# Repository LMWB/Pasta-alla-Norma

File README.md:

# Pasta_alla_Norma
Circular shaped RGB-LED PCB with integrated Microcontroller and EEPROM

# cubeIDE Setting for evaluate used flash size
```arm-none-eabi-nm --size-sort --print-size "RGB_Ring_LimbusZero.elf" > "RGB_Ring_LimbusZero.sizes"```  

- T / t → Flash (code)  
- R / r → Flash (read-only const)  
- D / d → RAM (with init in Flash)  
- B / b → RAM only (zero-init)  
- W / w → Weak (depends where resolved, often Flash functions)  

# Fassung
E27 bedeutet Edison Fassung 27 mm (siehe Zeichnung).  
Ein zylindrischer Stempel der in die Fassung passt ohne Gewinde, sollte 30mm Lange haben und 24mm Durchmesser.

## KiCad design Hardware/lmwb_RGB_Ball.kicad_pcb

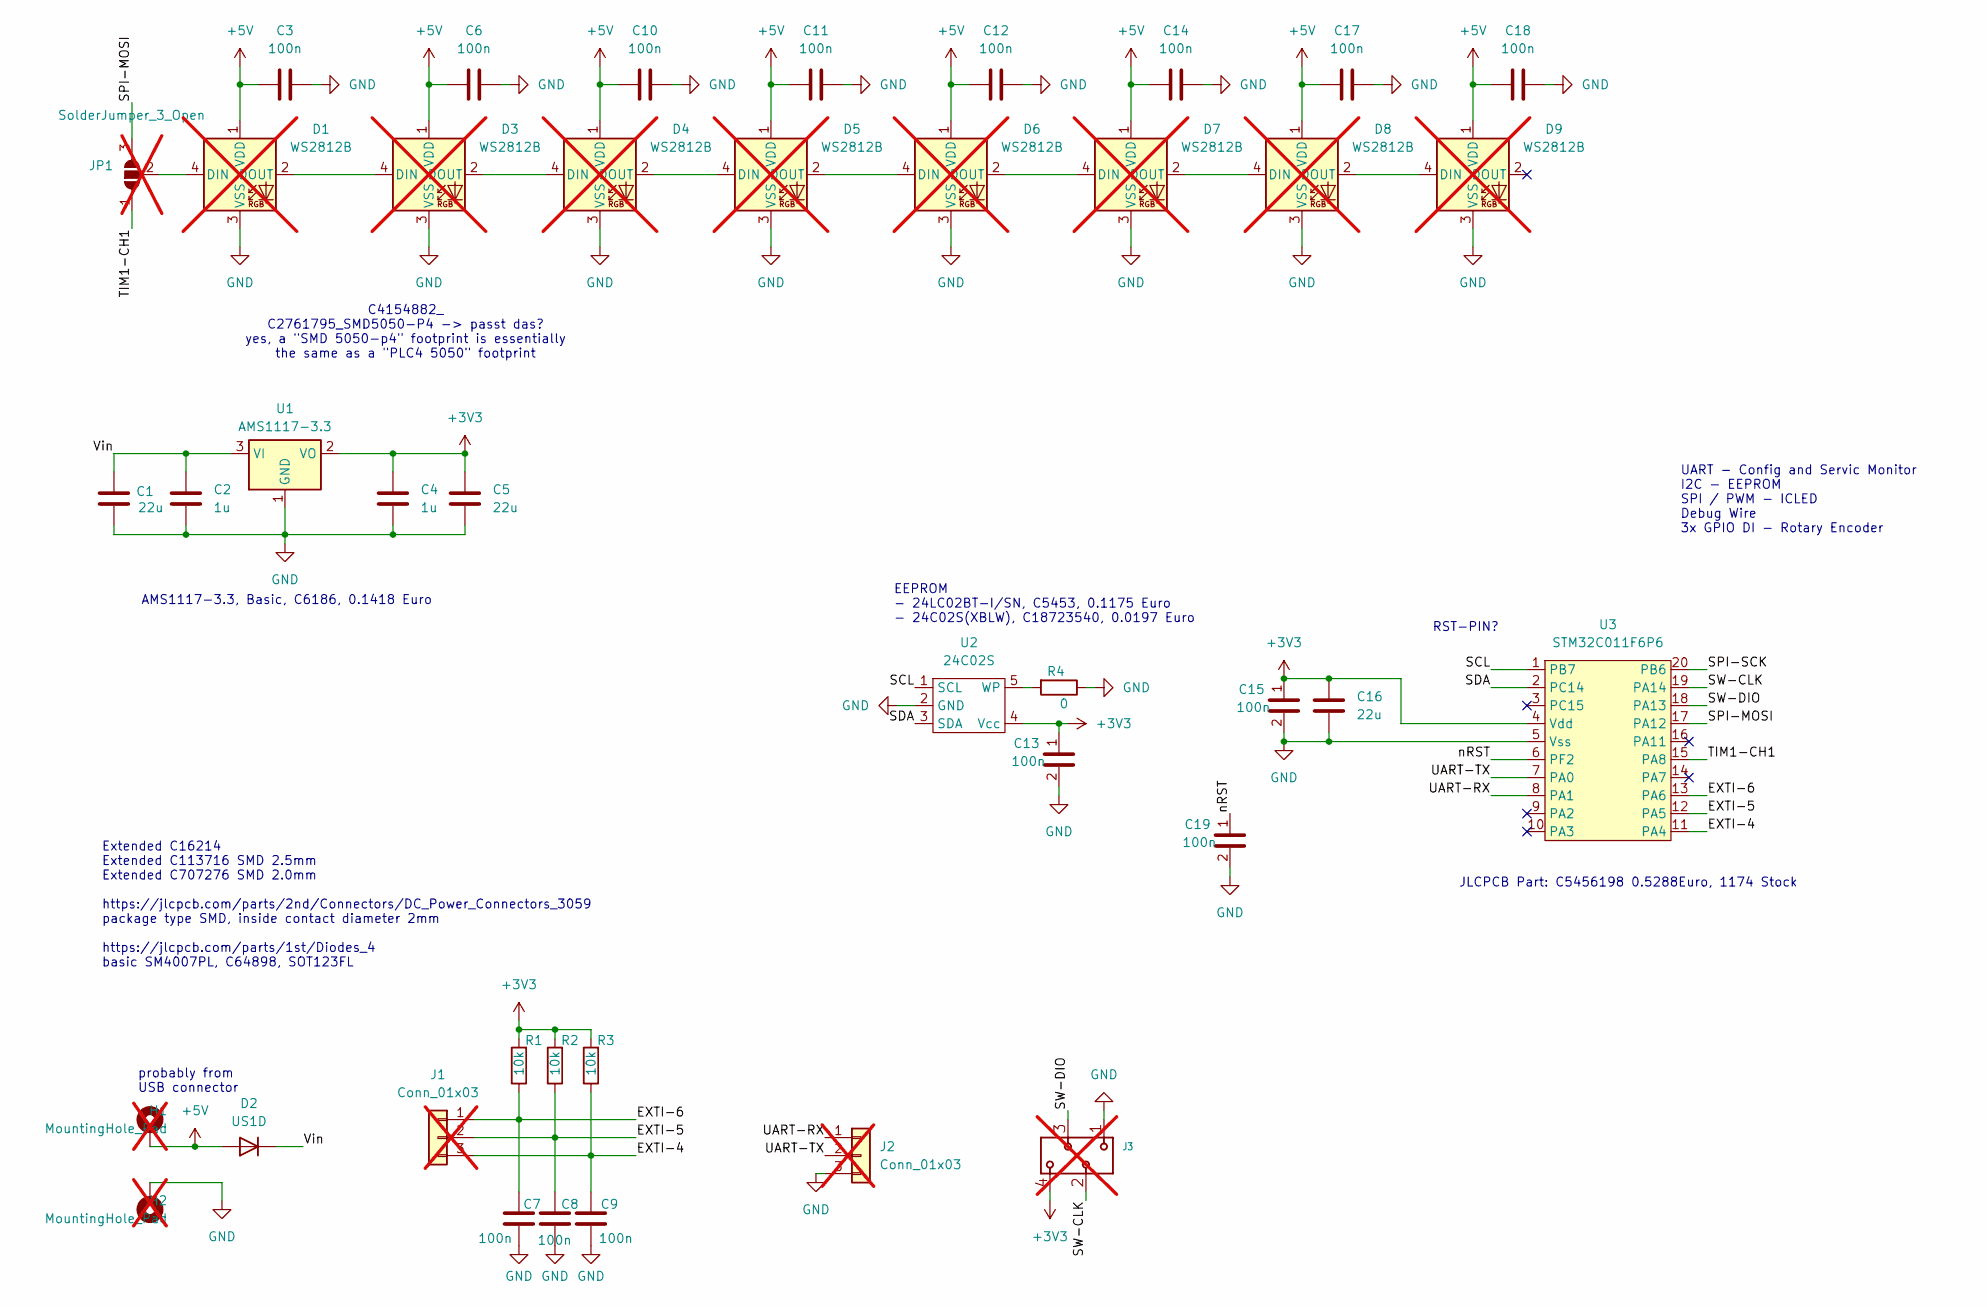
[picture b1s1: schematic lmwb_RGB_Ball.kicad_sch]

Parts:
C1, C5, C16: 22u; C_0805_2012Metric; LCSC PN C45783
C2, C4: 1u; C_0805_2012Metric; LCSC PN C28323
C3, C6, C7, C8, C9, C10, C11, C12, C13, C14, C15, C17, C18, C19: 100n; C_0805_2012Metric; LCSC PN C49678
D1, D3, D4, D5, D6, D7, D8, D9: WS2812B; LED_WS2812B_PLCC4_5.0x5.0mm_P3.2mm; LCSC PN C2761795; not fitted
D2: US1D; D_SMA; LCSC PN C95872
H1, H2: MountingHole_Pad; MountingHole_4.3mm_M4_Pad; not fitted
J1, J2: Conn_01x03; PinHeader_1x03_P2.54mm_Vertical; not fitted
J3: 490107670412_DEBUGGING; not fitted
JP1: SolderJumper_3_Open; SolderJumper-3_P1.3mm_Open_RoundedPad1.0x1.5mm; not fitted
R1, R2, R3: 10k; R_0805_2012Metric; LCSC PN C17414
R4: 0; R_0805_2012Metric; LCSC PN C17477
U1: AMS1117-3.3; SOT-223-3_TabPin2; LCSC PN C6186
U2: 24C02S; SOT-23-5; LCSC PN C18723540
U3: STM32C011F6P6; TSSOP-20_4.4x6.5mm_P0.65mm; LCSC PN C5456198

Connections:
+3V3: C4.1, C5.1, C13.1, C15.1, C16.1, J3.4, R1.2, R2.2, R3.2, U1.2 (VO), U2.4 (Vcc), U3.4 (Vdd)
+5V: C3.1, C6.1, C10.1, C11.1, C12.1, C14.1, C17.1, C18.1, D1.1 (VDD), D2.2 (A), D3.1 (VDD), D4.1 (VDD), D5.1 (VDD), D6.1 (VDD), D7.1 (VDD), D8.1 (VDD), D9.1 (VDD), H1.1
/EXTI-4: C9.1, J1.3, R3.1, U3.11 (PA4)
/EXTI-5: C8.1, J1.2, R2.1, U3.12 (PA5)
/EXTI-6: C7.1, J1.1, R1.1, U3.13 (PA6)
/SCL: U2.1 (SCL), U3.1 (PB7)
/SDA: U2.3 (SDA), U3.2 (PC14)
/SPI-MOSI: JP1.3 (B), U3.17 (PA12)
/SPI-SCK: U3.20 (PB6)
/SW-CLK: J3.2, U3.19 (PA14)
/SW-DIO: J3.3, U3.18 (PA13)
/TIM1-CH1: JP1.1 (A), U3.15 (PA8)
/UART-RX: J2.1, U3.8 (PA1)
/UART-TX: J2.2, U3.7 (PA0)
/Vin: C1.1, C2.1, D2.1 (K), U1.3 (VI)
/nRST: C19.1, U3.6 (PF2)
GND: C1.2, C2.2, C3.2, C4.2, C5.2, C6.2, C7.2, C8.2, C9.2, C10.2, C11.2, C12.2, C13.2, C14.2, C15.2, C16.2, C17.2, C18.2, C19.2, D1.3 (VSS), D3.3 (VSS), D4.3 (VSS), D5.3 (VSS), D6.3 (VSS), D7.3 (VSS), D8.3 (VSS), D9.3 (VSS), H2.1, J2.3, J3.1, R4.1, U1.1 (GND), U2.2 (GND), U3.5 (Vss)
unnamed: D1.4 (DIN), JP1.2 (C)
unnamed: D1.2 (DOUT), D3.4 (DIN)
unnamed: D3.2 (DOUT), D4.4 (DIN)
unnamed: D4.2 (DOUT), D5.4 (DIN)
unnamed: D5.2 (DOUT), D6.4 (DIN)
unnamed: D6.2 (DOUT), D7.4 (DIN)
unnamed: D7.2 (DOUT), D8.4 (DIN)
unnamed: D8.2 (DOUT), D9.4 (DIN)
unnamed: R4.2, U2.5 (WP)

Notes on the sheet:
UART - Config and Servic Monitor I2C - EEPROM SPI / PWM - ICLED Debug Wire 3x GPIO DI - Rotary Encoder
probably from USB connector
EEPROM - 24LC02BT-I/SN, C5453, 0.1175 Euro - 24C02S(XBLW), C18723540, 0.0197 Euro
RST-PIN?
AMS1117-3.3, Basic, C6186, 0.1418 Euro
JLCPCB Part: C5456198 0.5288Euro, 1174 Stock
Extended C16214 Extended C113716 SMD 2.5mm Extended C707276 SMD 2.0mm https://jlcpcb.com/parts/2nd/Connectors/DC_Power_Connectors_3059 package type SMD, inside contact diameter 2mm https://jlcpcb.com/parts/1st/Diodes_4 basic SM4007PL, C64898, SOT123FL
C4154882_ C2761795_SMD5050-P4 -> passt das? yes, a "SMD 5050-p4" footprint is essentially the same as a "PLC4 5050" footprint

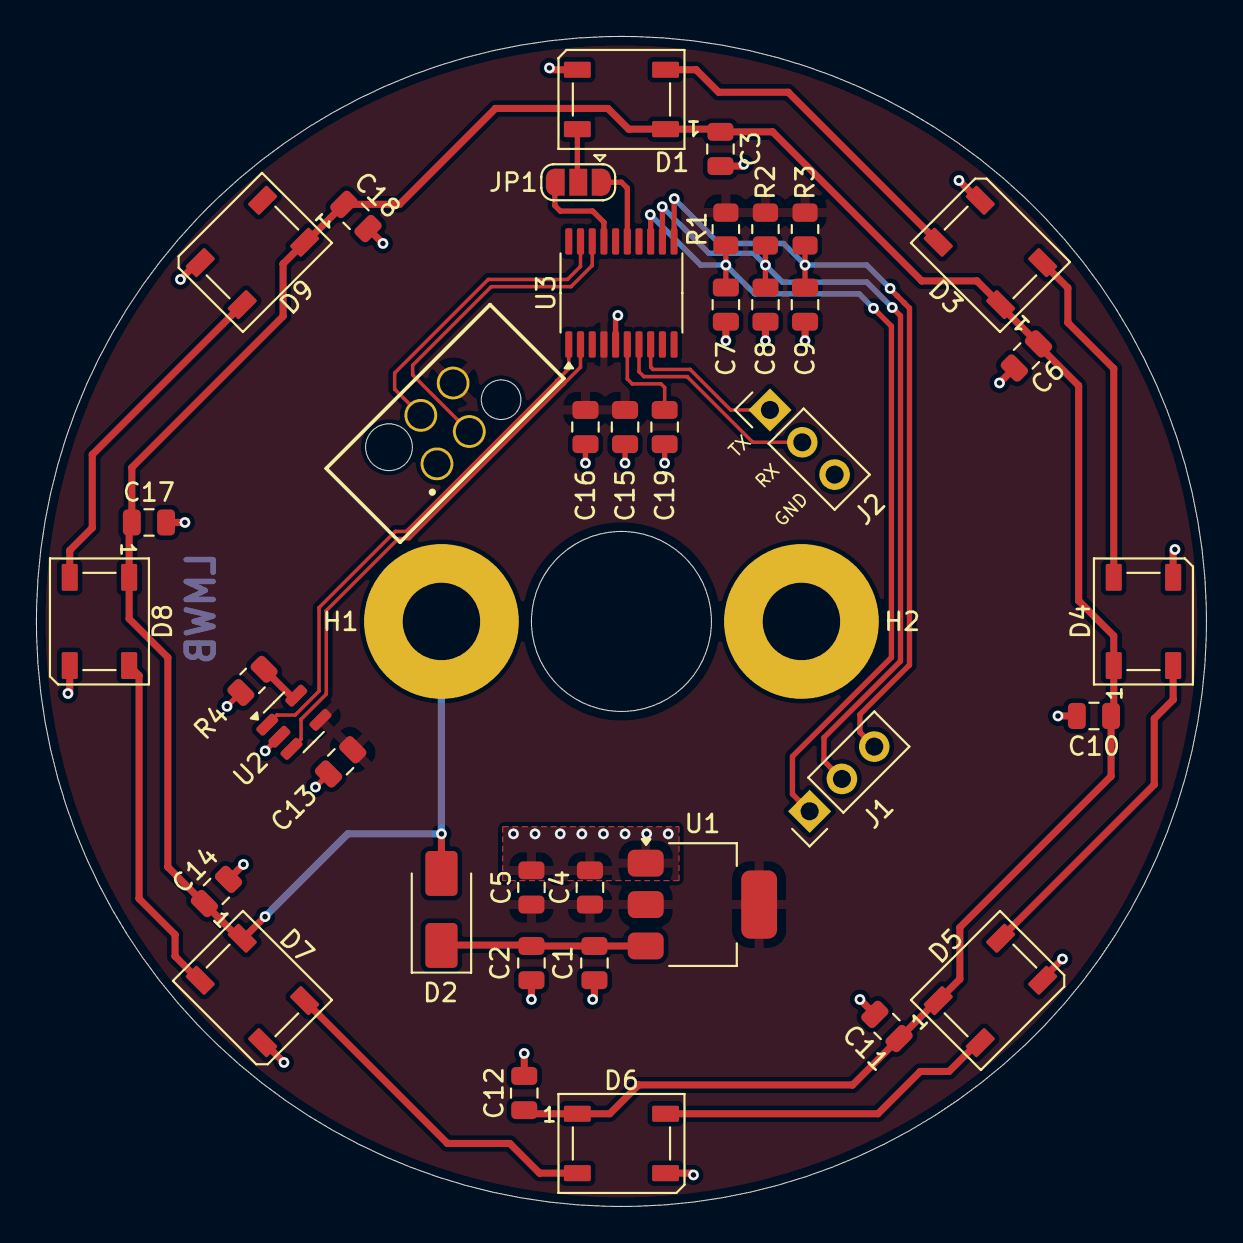
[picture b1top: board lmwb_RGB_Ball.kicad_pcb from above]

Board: 2 copper layers, 65.0 x 65.0 mm, 41 parts (0 on the bottom side), 25 nets.

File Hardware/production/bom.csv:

Designator,Footprint,Quantity,Value,LCSC Part #
"C1, C16, C5",0805,3,22u,C45783
"C10, C11, C12, C13, C14, C15, C17, C18, C19, C3, C6, C7, C8, C9",0805,14,100n,C49678
"C2, C4",0805,2,1u,C28323
D2,D_SMA,1,US1D,C95872
"R1, R2, R3",0805,3,10k,C17414
R4,0805,1,0,C17477
U1,SOT-223-3_TabPin2,1,AMS1117-3.3,C6186
U2,SOT-23-5,1,24C02S,C18723540
U3,TSSOP-20_4.4x6.5mm_P0.65mm,1,STM32C011F6P6,C5456198

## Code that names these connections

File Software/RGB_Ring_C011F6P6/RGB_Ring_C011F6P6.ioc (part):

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Mcu.Name=STM32C011F(4-6)Px
Mcu.Package=TSSOP20
Mcu.UserName=STM32C011F6Px
PA0.Signal=USART1_TX
PA1.Signal=USART1_RX
PA12\ [PA10].Mode=TX_Only_Simplex_Unidirect_Master
PA12\ [PA10].Signal=SPI1_MOSI
PA13.Mode=Serial_Wire
PA13.Signal=DEBUG_SWDIO
PA14-BOOT0.Mode=Serial_Wire
PA14-BOOT0.Signal=DEBUG_SWCLK
PA4.GPIOParameters=GPIO_Label
PA4.GPIO_Label=IN2
PA4.Signal=GPIO_Input
PA5.GPIOParameters=GPIO_Label
PA5.GPIO_Label=OUT1
PA5.Signal=GPIO_Output
PA6.GPIOParameters=GPIO_Label
PA6.GPIO_Label=IN1
PA6.Signal=GPIO_Input
PA8.GPIOParameters=GPIO_Speed,GPIO_PuPd
PA8.GPIO_PuPd=GPIO_PULLUP
PA8.GPIO_Speed=GPIO_SPEED_FREQ_VERY_HIGH
PA8.Signal=S_TIM1_CH1
PB6.GPIOParameters=GPIO_Speed,GPIO_PuPd
PB6.GPIO_PuPd=GPIO_PULLDOWN
PB6.GPIO_Speed=GPIO_SPEED_FREQ_VERY_HIGH
PB6.Mode=TX_Only_Simplex_Unidirect_Master
PB6.Signal=SPI1_SCK
PB7.Signal=I2C1_SCL
PC14-OSCX_IN\ (PC14).Signal=I2C1_SDA
RCC.HSE_VALUE=8000000
RCC.SYSCLKFreq_VALUE=48000000
board=custom

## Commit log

2025-08-28 created project structure
2025-09-14 did some routing
2025-09-14 added freeCAD Model
2025-09-14 did some readme
2025-09-22 added CAD files adn step files
2025-09-22 added LimbusZero cubeMX project
2025-09-22 added C-libraries
2025-09-25 added F04xx project, coded firmware, progress on layout
2025-09-26 progress on layout
2025-09-26 order pcb and assambly
2025-09-28 moved functional code to rgb_ball.c
2025-09-28 removed math.c and created gamma-look-up-table
2025-09-28 modified python script
2025-09-29 modified readme
2025-10-06 added rainbow fade
2025-10-07 added sunstorm loop
2025-10-11 testing sunstorm fade
2025-10-11 LED toggle wrapper
2025-10-11 read / write pin wrapper
2025-10-11 add libs to tarket project
2025-10-11 add application to target project
2025-10-17 software adjustments to fit target PCB
2025-10-17 synch SW changes from target PCB to LimbusZero Dev Platform
2025-10-17 update cubeMX project for SPI
2025-10-17 make SPI driver work on Limbus Zero
2025-10-17 make SPI driver work on C011-project
2025-10-17 does not help, return to PWM
2025-10-17 added docs and manual
2025-10-17 after hot resoldering now 8 LED working
2025-10-17 PWM works best, spi has timing issus
2025-10-17 little bit clean up unused code
2025-10-17 probaly going to removing SPI driver
2025-10-17 review technical docs
2025-10-27 added haunted pickle function
2025-10-29 tested haunted pickle RGB fading
2026-01-16 edit comment in PCB
